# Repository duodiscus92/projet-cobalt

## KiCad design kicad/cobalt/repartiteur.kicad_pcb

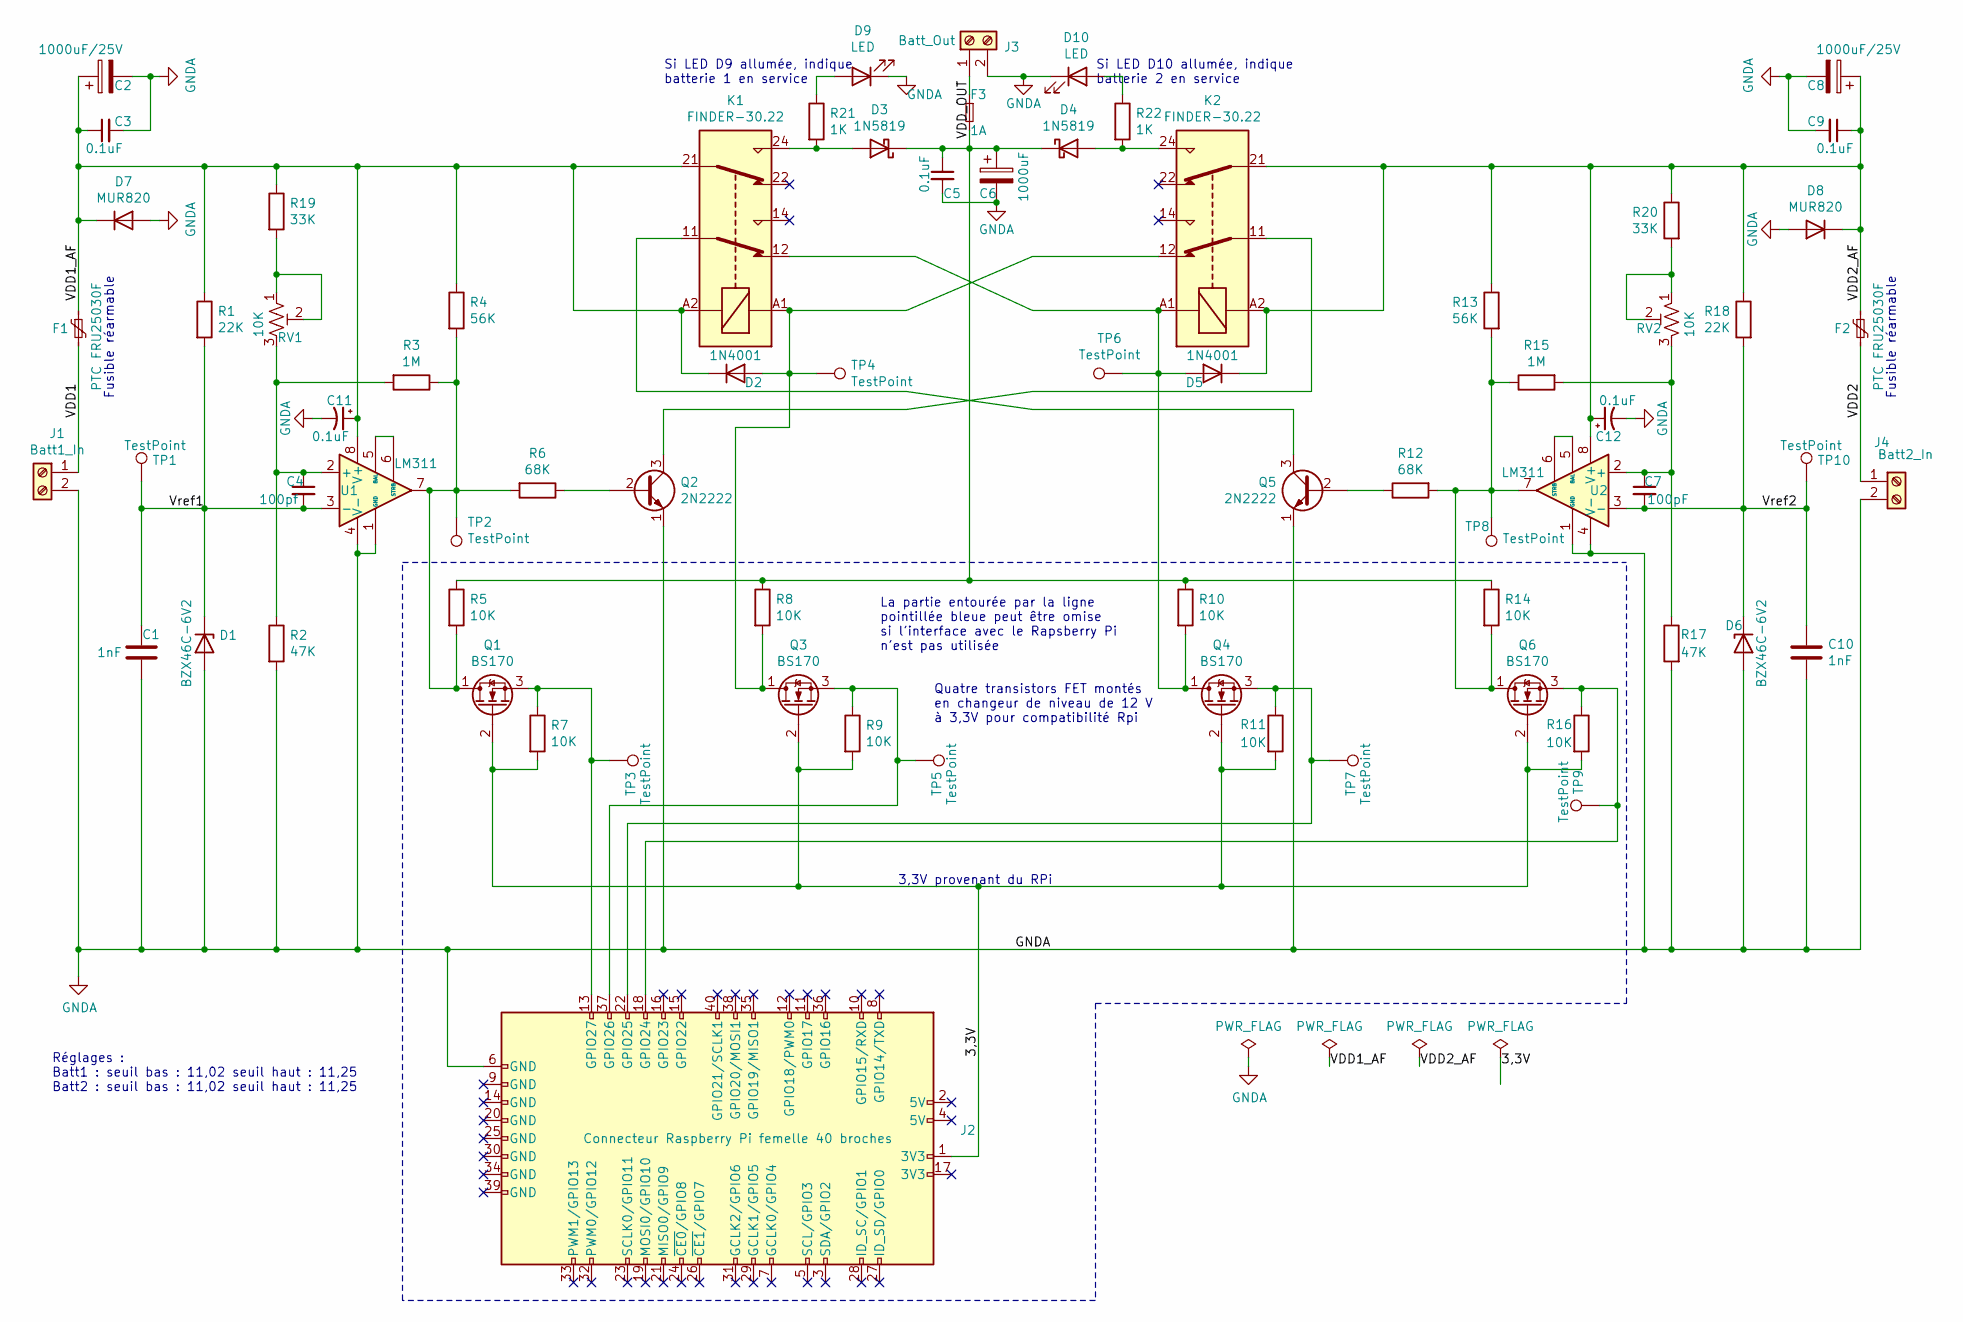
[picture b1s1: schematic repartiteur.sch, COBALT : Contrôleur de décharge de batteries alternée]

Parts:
C1, C10: 1nF; C_Rect_L7.2mm_W4.5mm_P5.00mm_FKS2_FKP2_MKS2_MKP2
C2, C8: 1000uF/25V; CP_Radial_D10.0mm_P5.00mm
C3, C5, C9, C11, C12: 0.1uF; C_Rect_L7.2mm_W2.5mm_P5.00mm_FKS2_FKP2_MKS2_MKP2
C4: 100pf; C_Rect_L7.2mm_W4.5mm_P5.00mm_FKS2_FKP2_MKS2_MKP2
C6: 1000uF; CP_Radial_D10.0mm_P5.00mm
C7: 100pF; C_Rect_L7.2mm_W4.5mm_P5.00mm_FKS2_FKP2_MKS2_MKP2
D1, D6: BZX46C-6V2; D_DO-35_SOD27_P10.16mm_Horizontal
D2, D5: 1N4001; D_DO-41_SOD81_P10.16mm_Horizontal
D3, D4: 1N5819; D_DO-41_SOD81_P10.16mm_Horizontal
D7, D8: MUR820; TO-220-2_Vertical
D9, D10: LED; LED_D5.0mm
F1, F2: PTC FRU25030F; C_Rect_L7.0mm_W3.5mm_P5.00mm
F3: 1A; Fuseholder_TR5_Littelfuse_No560_No460
J1: Batt1_In; TerminalBlock_bornier-2_P5.08mm
J2: Connecteur Raspberry Pi femelle 40 broches; PinHeader_2x20_P2.54mm_Vertical
J3: Batt_Out; TerminalBlock_bornier-2_P5.08mm
J4: Batt2_In; TerminalBlock_bornier-2_P5.08mm
K1, K2: FINDER-30.22; Relay_DPDT_Finder_30.22
Q1, Q3, Q4, Q6: BS170; TO-18-3
Q2, Q5: 2N2222; TO-18-3
R1, R18: 22K; R_Axial_DIN0207_L6.3mm_D2.5mm_P7.62mm_Horizontal
R2, R17: 47K; R_Axial_DIN0207_L6.3mm_D2.5mm_P7.62mm_Horizontal
R3, R15: 1M; R_Axial_DIN0207_L6.3mm_D2.5mm_P7.62mm_Horizontal
R4, R13: 56K; R_Axial_DIN0207_L6.3mm_D2.5mm_P7.62mm_Horizontal
R5, R7, R8, R9, R10, R11, R14, R16: 10K; R_Axial_DIN0207_L6.3mm_D2.5mm_P7.62mm_Horizontal
R6, R12: 68K; R_Axial_DIN0207_L6.3mm_D2.5mm_P7.62mm_Horizontal
R19, R20: 33K; R_Axial_DIN0207_L6.3mm_D2.5mm_P7.62mm_Horizontal
R21, R22: 1K; R_Axial_DIN0207_L6.3mm_D2.5mm_P7.62mm_Horizontal
RV1, RV2: 10K; Potentiometer_Bourns_3296W_Vertical
TP1, TP2, TP3, TP4, TP5, TP6, TP7, TP8, TP9, TP10: TestPoint; TestPoint_Pad_2.0x2.0mm
U1, U2: LM311; DIP-8_W7.62mm_Socket_LongPads

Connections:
/3,3V: J2.1 (3V3), Q1.2 (G), Q3.2 (G), Q4.2 (G), Q6.2 (G), R7.2, R9.2, R11.2, R16.2
/VDD1: F1.2, J1.1
/VDD1_AF: C2.1, C3.1, C11.1, D2.1 (K), D7.1 (K), F1.1, K1.21, K1.A2, R1.1, R4.1, R19.1, U1.8 (V+)
/VDD2: F2.2, J4.1
/VDD2_AF: C8.1, C9.1, C12.1, D5.1 (K), D8.1 (K), F2.1, K2.21, K2.A2, R13.1, R18.1, R20.1, U2.8 (V+)
/VDD_OUT: C5.1, C6.1, D3.1 (K), D4.1 (K), F3.2, R5.1, R8.1, R10.1, R14.1
/Vref1: C1.1, C4.2, D1.1 (K), R1.2, TP1.1, U1.3 (-)
/Vref2: C7.2, C10.1, D6.1 (K), R18.2, TP10.1, U2.3 (-)
GNDA: C1.2, C2.2, C3.2, C5.2, C6.2, C8.2, C9.2, C10.2, C11.2, C12.2, D1.2 (A), D6.2 (A), D7.2 (A), D8.2 (A), D9.1 (K), D10.1 (K), J1.2, J2.6 (GND), J3.2, J4.2, Q2.1 (E), Q5.1 (E), R2.2, R17.2, U1.1 (GND), U1.4 (V-), U2.1 (GND), U2.4 (V-)
unnamed: C4.1, R2.1, R3.2, RV1.3, U1.2 (+)
unnamed: C7.1, R15.2, R17.1, RV2.3, U2.2 (+)
unnamed: D2.2 (A), K1.A1, K2.12, Q3.1 (D), R8.2, TP4.1
unnamed: D3.2 (A), K1.24, R21.2
unnamed: D4.2 (A), K2.24, R22.2
unnamed: D5.2 (A), K1.12, K2.A1, Q4.1 (D), R10.2, TP6.1
unnamed: D9.2 (A), R21.1
unnamed: D10.2 (A), R22.1
unnamed: F3.1, J3.1
unnamed: J2.13 (GPIO27), Q1.3 (S), R7.1, TP3.1
unnamed: J2.18 (GPIO24), Q6.3 (S), R16.1, TP9.1
unnamed: J2.22 (GPIO25), Q4.3 (S), R11.1, TP7.1
unnamed: J2.37 (GPIO26), Q3.3 (S), R9.1, TP5.1
unnamed: K1.11, Q5.3 (C)
unnamed: K2.11, Q2.3 (C)
unnamed: Q1.1 (D), R3.1, R4.2, R5.2, R6.2, TP2.1, U1.7
unnamed: Q2.2 (B), R6.1
unnamed: Q5.2 (B), R12.1
unnamed: Q6.1 (D), R12.2, R13.2, R14.2, R15.1, TP8.1, U2.7
unnamed: R19.2, RV1.1, RV1.2
unnamed: R20.2, RV2.1, RV2.2
unnamed: U1.5 (BAL), U1.6 (STRB)
unnamed: U2.5 (BAL), U2.6 (STRB)

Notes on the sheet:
La partie entourée par la ligne pointillée bleue peut être omise si l'interface avec le Rapsberry Pi n'est pas utilisée
Quatre transistors FET montés en changeur de niveau de 12 V à 3,3V pour compatibilité Rpi
3,3V provenant du RPi
Réglages : Batt1 : seuil bas : 11,02 seuil haut : 11,25 Batt2 : seuil bas : 11,02 seuil haut : 11,25
Fusible réarmable
Si LED D9 allumée, indique batterie 1 en service
Si LED D10 allumée, indique batterie 2 en service

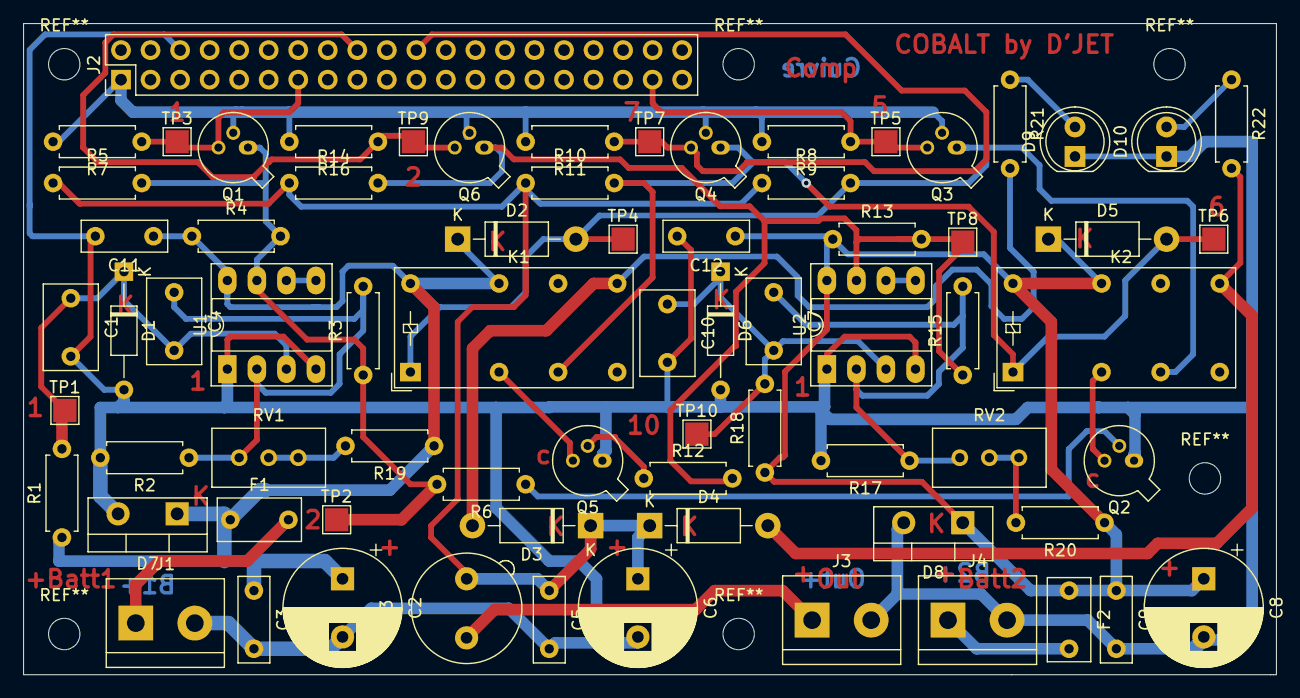
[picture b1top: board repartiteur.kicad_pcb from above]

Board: 2 copper layers, 107.8 x 56.0 mm, 73 parts (0 on the bottom side), 32 nets.

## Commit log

2021-02-05 ajout notice COBALT
